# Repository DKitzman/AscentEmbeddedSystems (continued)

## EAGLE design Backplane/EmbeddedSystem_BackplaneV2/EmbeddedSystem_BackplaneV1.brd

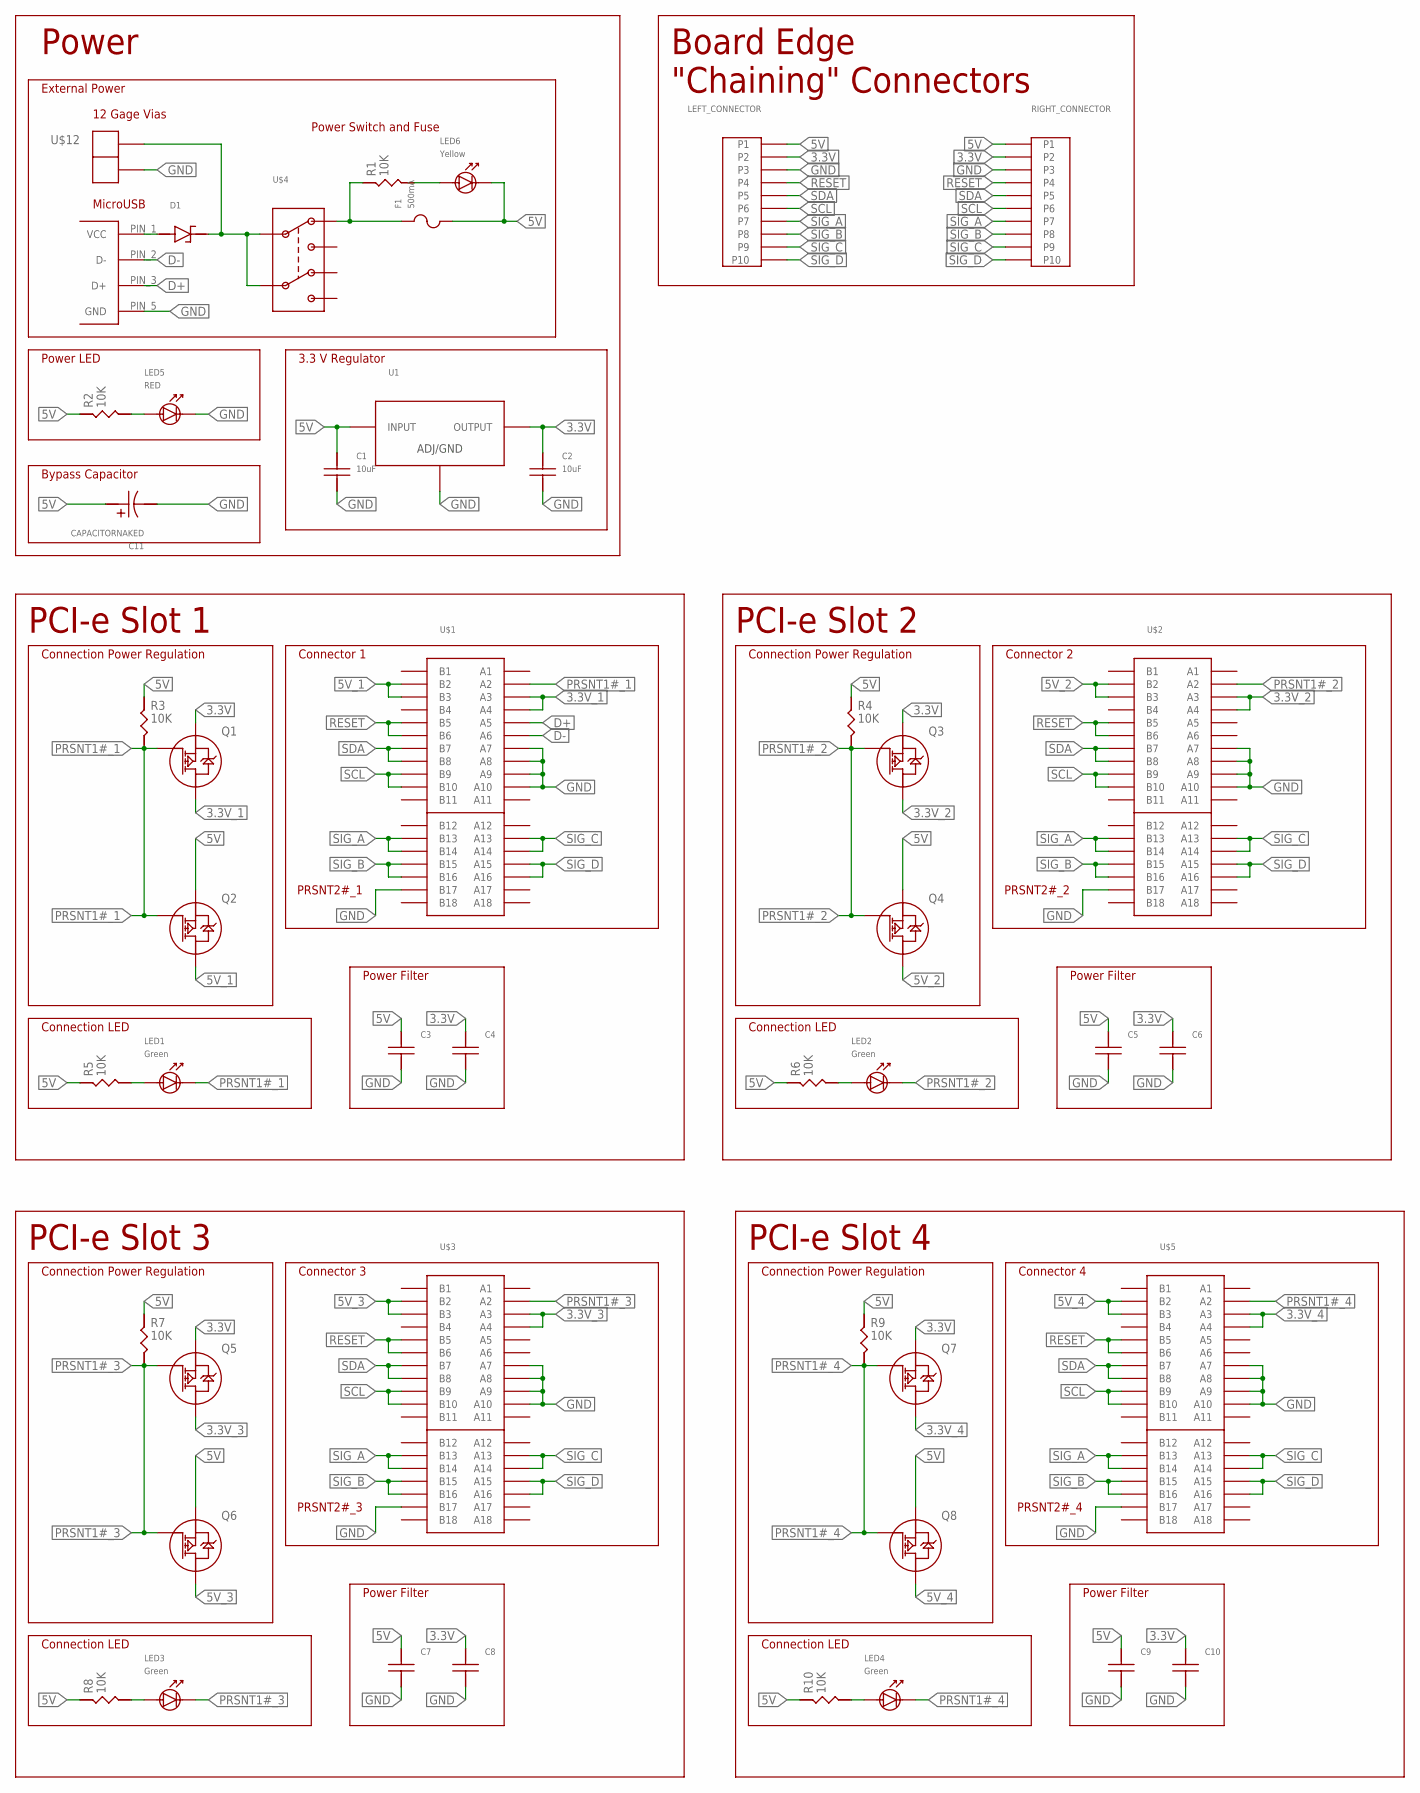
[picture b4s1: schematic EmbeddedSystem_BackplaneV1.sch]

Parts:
C1, C2: 10uF; 0805_STACKPOLERESISTOR
C3, C4, C5, C6, C7, C8, C9, C10: CAPACITOR-UNPOLARIZED0805; 0805_STACKPOLERESISTOR
C11: CAPACITORNAKED; ESK_H4_CAPACITOR_NAKED
D1: DIODE_SCHOTTKYSOD-123; SOD-123
F1: 500mA; TYPE_C1Q_FUSE
LED1, LED2, LED3, LED4: Green; 0805_LED
LED5: RED; 0805_LED
LED6: Yellow; 0805_LED
LEFT_CONNECTOR: 10PIN-HEADER; 10PIN_HEADER
Q1, Q2, Q3, Q4, Q5, Q6, Q7, Q8: PMOSSOT-23; SOT-23
R1, R2, R3, R4, R5, R6, R7, R8, R9, R10: 10K; 0805_STACKPOLERESISTOR
RIGHT_CONNECTOR: 10PIN-HEADER; 10PIN_HEADER
U1: VOLTAGE_REGULATOR; SOT223
U$1, U$2, U$3, U$5: PCI-E_X1; PCIE_X1
U$4: SWITCH_DPDT; SWITCH_GF-126
U$10: USBMICROB; USBMICROB-PAC
U$12: 2PIN-HEADER16GAGE; 2PIN_16GAGE

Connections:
3.3V: C2.P$1, C4.P$1, C6.P$1, C8.P$1, C10.P$1, LEFT_CONNECTOR.P2, Q1.S, Q3.S, Q5.S, Q7.S, RIGHT_CONNECTOR.P2, U1.P2 (OUTPUT), U1.TOP (OUTPUT)
3.3V_1: Q1.D, U$1.A3, U$1.A4
3.3V_2: Q3.D, U$2.A3, U$2.A4
3.3V_3: Q5.D, U$3.A3, U$3.A4
3.3V_4: Q7.D, U$5.A3, U$5.A4
5V: C1.P$1, C3.P$1, C5.P$1, C7.P$1, C9.P$1, C11.POSITIVE_PAD (POSITIVE_LEAD), F1.P$2, LED6.CATHODE, LEFT_CONNECTOR.P1, Q2.S, Q4.S, Q6.S, Q8.S, R2.P$1, R3.P$1, R4.P$1, R5.P$1, R6.P$1, R7.P$1, R8.P$1, R9.P$1, R10.P$1, RIGHT_CONNECTOR.P1, U1.P3 (INPUT)
5V_1: Q2.D, U$1.B2, U$1.B3
5V_2: Q4.D, U$2.B2, U$2.B3
5V_3: Q6.D, U$3.B2, U$3.B3
5V_4: Q8.D, U$5.B2, U$5.B3
5V_SUPPLY: D1.CATHODE, U$4.P1_C, U$4.P2_C, U$12.P1
D+: U$1.A5, U$10.PIN_3 (D+)
D-: U$1.A6, U$10.PIN_2 (D-)
GND: C1.P$2, C2.P$2, C3.P$2, C4.P$2, C5.P$2, C6.P$2, C7.P$2, C8.P$2, C9.P$2, C10.P$2, C11.NEGATIVE_PAD (NEGATIVE_LEAD), LED5.CATHODE, LEFT_CONNECTOR.P3, RIGHT_CONNECTOR.P3, U1.P1 (ADJ/GND), U$1.A7, U$1.A8, U$1.A9, U$1.A10, U$1.B17, U$2.A7, U$2.A8, U$2.A9, U$2.A10, U$2.B17, U$3.A7, U$3.A8, U$3.A9, U$3.A10, U$3.B17, U$5.A7, U$5.A8, U$5.A9, U$5.A10, U$5.B17, U$10.PIN_5 (GND), U$12.P2
unnamed: LED5.ANODE, R2.P$2
unnamed: F1.P$1, R1.P$1, U$4.P1_1
unnamed: LED6.ANODE, R1.P$2
unnamed: LED1.ANODE, R5.P$2
unnamed: D1.ANODE, U$10.PIN_1 (VCC)
unnamed: LED2.ANODE, R6.P$2
unnamed: LED3.ANODE, R8.P$2
unnamed: LED4.ANODE, R10.P$2
PRSNT1#_1: LED1.CATHODE, Q1.G (G(1)), Q2.G (G(1)), R3.P$2, U$1.A2
PRSNT1#_2: LED2.CATHODE, Q3.G (G(1)), Q4.G (G(1)), R4.P$2, U$2.A2
PRSNT1#_3: LED3.CATHODE, Q5.G (G(1)), Q6.G (G(1)), R7.P$2, U$3.A2
PRSNT1#_4: LED4.CATHODE, Q7.G (G(1)), Q8.G (G(1)), R9.P$2, U$5.A2
RESET: LEFT_CONNECTOR.P4, RIGHT_CONNECTOR.P4, U$1.B5, U$1.B6, U$2.B5, U$2.B6, U$3.B5, U$3.B6, U$5.B5, U$5.B6
SCL: LEFT_CONNECTOR.P6, RIGHT_CONNECTOR.P6, U$1.B9, U$1.B10, U$2.B9, U$2.B10, U$3.B9, U$3.B10, U$5.B9, U$5.B10
SDA: LEFT_CONNECTOR.P5, RIGHT_CONNECTOR.P5, U$1.B7, U$1.B8, U$2.B7, U$2.B8, U$3.B7, U$3.B8, U$5.B7, U$5.B8
SIG_A: LEFT_CONNECTOR.P7, RIGHT_CONNECTOR.P7, U$1.B13, U$1.B14, U$2.B13, U$2.B14, U$3.B13, U$3.B14, U$5.B13, U$5.B14
SIG_B: LEFT_CONNECTOR.P8, RIGHT_CONNECTOR.P8, U$1.B15, U$1.B16, U$2.B15, U$2.B16, U$3.B15, U$3.B16, U$5.B15, U$5.B16
SIG_C: LEFT_CONNECTOR.P9, RIGHT_CONNECTOR.P9, U$1.A13, U$1.A14, U$2.A13, U$2.A14, U$3.A13, U$3.A14, U$5.A13, U$5.A14
SIG_D: LEFT_CONNECTOR.P10, RIGHT_CONNECTOR.P10, U$1.A15, U$1.A16, U$2.A15, U$2.A16, U$3.A15, U$3.A16, U$5.A15, U$5.A16

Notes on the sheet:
Connector 1
PRSNT2#_1
Power LED
External Power
12 Gage Vias
MicroUSB
Power Switch and Fuse
3.3 V Regulator
Power
Connection LED
Connection Power Regulation
PCI-e Slot 1
Board Edge "Chaining" Connectors
Power Filter
Connector 2
PRSNT2#_2
PCI-e Slot 2
Connector 3
PRSNT2#_3
PCI-e Slot 3
Connector 4
PRSNT2#_4
PCI-e Slot 4
Bypass Capacitor

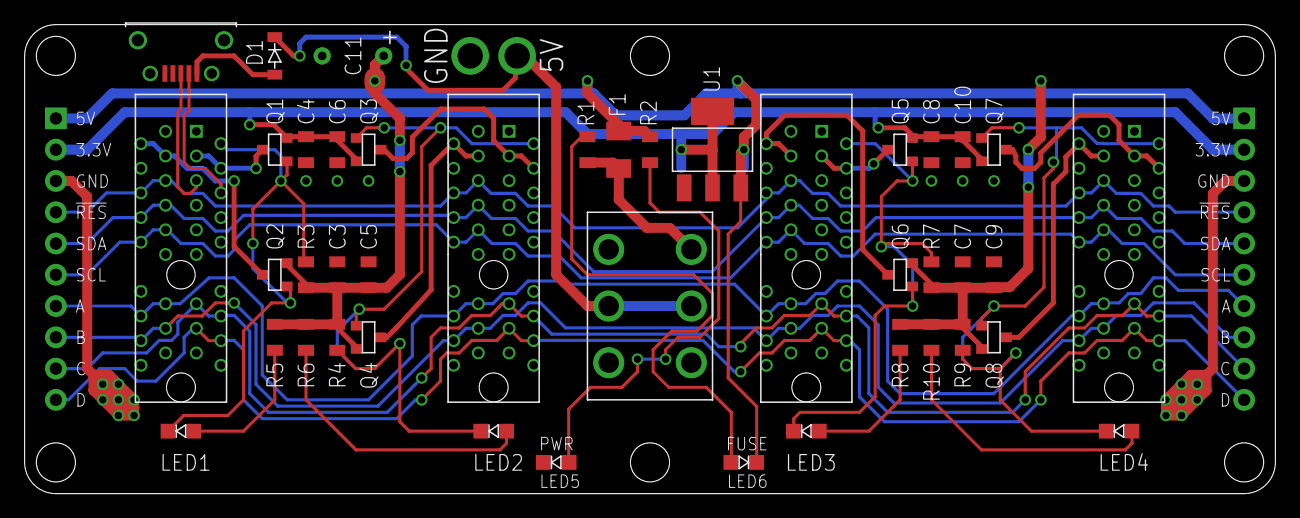
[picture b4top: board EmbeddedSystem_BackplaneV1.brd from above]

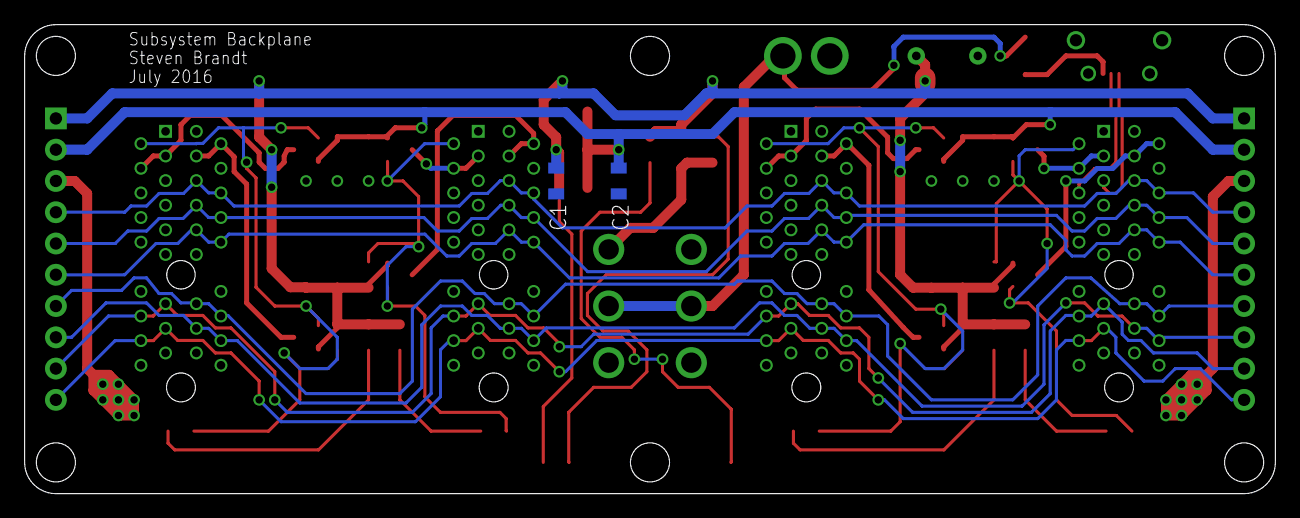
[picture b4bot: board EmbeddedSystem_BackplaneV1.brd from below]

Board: 2 copper layers, 101.6 x 38.1 mm, 47 parts (2 on the bottom side), 33 nets.

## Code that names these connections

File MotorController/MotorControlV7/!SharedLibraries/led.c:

#include <avr/io.h>
#include "led.h"

#define CMD_MASK (1<<2)
#define PING_MASK (1<<1)
#define ALIVE_MASK (1<<0)

/* /// PIN USAGE ///
PORTA - data out
PB0 - ALIVE
PB1 - PING
PB2 - CMD
 */

void led_init()
{
	PORTA.OUTSET = 0xFF;
	PORTA.DIRSET = 0xFF;

	PORTB.OUTSET = 0x07;
	PORTB.DIRSET = 0x07;
}

void led_cmdOn()
{
	PORTB.OUTCLR = CMD_MASK;
}
void led_cmdOff()
{
	PORTB.OUTSET = CMD_MASK;
}
void led_cmdToggle()
{
	PORTB.OUTTGL = CMD_MASK;
}

void led_pingOn()
{
	PORTB.OUTCLR = PING_MASK;
}
void led_pingOff()
{
	PORTB.OUTSET = PING_MASK;
}
void led_pingToggle()
{
	PORTB.OUTTGL = PING_MASK;
}

void led_aliveOn()
{
	PORTB.OUTCLR = ALIVE_MASK;
}
void led_aliveOff()
{
	PORTB.OUTSET = ALIVE_MASK;
}
void led_aliveToggle()
{
	PORTB.OUTTGL = ALIVE_MASK;
}

void led_dataOut(uint8_t value)
{
	PORTA.OUT = ~value;
}
void led_bitSet(uint8_t bit)
{
	PORTA.OUTCLR = (1<<bit);
}
void led_bitClear(uint8_t bit)
{
	PORTA.OUTSET = (1<<bit);
}
void led_bitToggle(uint8_t bit)
{
	PORTA.OUTTGL = (1<<bit);
}

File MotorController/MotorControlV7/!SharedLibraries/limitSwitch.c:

#include <avr/io.h>
#include "limitSwitch.h"

/* /// PERIPHERAL USAGE ///
 * None
 */

/* /// PIN USAGE ///
 * PE4	SW_A0
 * PE5	SW_B0
 *
 * PE6	SW_A1
 * PE7	SW_B1
 */

void limitSwitch_init()
{
	PORTE.DIRCLR = 0xF0;
	//Setting Pins 4-7 as totemPoll pullup
	PORTCFG.MPCMASK |= 0xF0;
	PORTE.PIN0CTRL = PORT_OPC_PULLUP_gc;
}

uint8_t atLimitA0()
{
	return (~PORTE.IN) & PIN4_bm;
}
uint8_t atLimitB0()
{
	return (~PORTE.IN) & PIN5_bm;
}

uint8_t atLimitA1()
{
	return (~PORTE.IN) & PIN6_bm;
}
uint8_t atLimitB1()
{
	return (~PORTE.IN) & PIN7_bm;
}

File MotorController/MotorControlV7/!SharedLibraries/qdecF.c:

#include <avr/io.h>
#include "qdecF.h"

#define DEGREES_PER_REV 360
#define CLOCK_CPU (uint32_t)32000000
#define PRESCALER 256

/* /// PERIPHERAL USAGE ///
 * TE0	qdec0 counter
 * TC1	freq0
 *
 * TF0	qdec1 counter
 * TD1	freq1
 */

/* /// PIN USAGE ///
 * PC4	QA0
 * PC5	QB0
 *
 * PD4	QA1
 * PD5	QB1
 */

static uint16_t cpr0 = 100;
static float lastVel0 = 0;

static uint16_t cpr1 = 100;
static float lastVel1 = 0;

void qdec_init(uint16_t cpr0p, uint16_t cpr1p)
{
	//Initializing qdec0
	cpr0 = cpr0p;
	PORTC.DIRCLR = PIN4_bm | PIN5_bm;

	// Set QDPH0 and QDPH1 sensing level.
	PORTCFG.MPCMASK = PIN4_bm | PIN5_bm;
	PORTC.PIN0CTRL = (PORTC.PIN0CTRL & ~PORT_ISC_gm) | PORT_ISC_LEVEL_gc;

	// Configure event
	EVSYS.CH0MUX = EVSYS_CHMUX_PORTC_PIN4_gc;
	EVSYS.CH0CTRL = EVSYS_QDEN_bm | EVSYS_DIGFILT_2SAMPLES_gc;

	// Configure TC as a quadrature counter.
	TCE0.CTRLD = (uint8_t) TC_EVACT_QDEC_gc | TC_EVSEL_CH0_gc;
	TCE0.CTRLA = TC_CLKSEL_DIV1_gc;

	// Configure channel 2 to input pin for freq calculation.
	EVSYS.CH1MUX = EVSYS_CHMUX_PORTC_PIN4_gc;
	EVSYS.CH1CTRL = EVSYS_DIGFILT_4SAMPLES_gc;

	// Configure TC to capture frequency.
	TCC1.CTRLD = (uint8_t) TC_EVACT_FRQ_gc | TC_EVSEL_CH1_gc;
	TCC1.CTRLB = TC1_CCAEN_bm;
	TCC1.CTRLA = TC_CLKSEL_DIV256_gc;


	//Initializing qdec1 
	cpr1 = cpr1p;
	PORTD.DIRCLR = PIN4_bm | PIN5_bm;

	// Set QDPH0 and QDPH1 sensing level.
	PORTCFG.MPCMASK = PIN4_bm | PIN5_bm;
	PORTD.PIN0CTRL = (PORTD.PIN0CTRL & ~PORT_ISC_gm) | PORT_ISC_LEVEL_gc;

	// Configure event
	EVSYS.CH2MUX = EVSYS_CHMUX_PORTD_PIN4_gc;
	EVSYS.CH2CTRL = EVSYS_QDEN_bm | EVSYS_DIGFILT_2SAMPLES_gc;

	// Configure TC as a quadrature counter.
	TCF0.CTRLD = (uint8_t) TC_EVACT_QDEC_gc | TC_EVSEL_CH2_gc;
	TCF0.CTRLA = TC_CLKSEL_DIV1_gc;

	// Configure channel 3 to input pin for freq calculation.
	EVSYS.CH3MUX = EVSYS_CHMUX_PORTD_PIN4_gc;
	EVSYS.CH3CTRL = EVSYS_DIGFILT_4SAMPLES_gc;

	// Configure TC to capture frequency.
	TCD1.CTRLD = (uint8_t) TC_EVACT_FRQ_gc | TC_EVSEL_CH3_gc;
	TCD1.CTRLB = TC1_CCAEN_bm;
	TCD1.CTRLA = TC_CLKSEL_DIV256_gc;

}

uint16_t qdec_pos0()
{
	return TCE0.CNT;
}
uint16_t qdec_pos1()
{
	return TCF0.CNT;
}

float qdec_vel0()
{
	if(TCC1.INTFLAGS & TC1_OVFIF_bm)
	{
		//TCC1.INTFLAGS |= TC1_OVFIF_bm;
		lastVel0 = 0;
	}
	else if(TCC1.INTFLAGS & TC1_CCAIF_bm)
	{
		lastVel0 = (DEGREES_PER_REV*(CLOCK_CPU/PRESCALER))/((float)cpr0*TCC1.CCA);
		if (TCE0.CTRLFSET & TC0_DIR_bm) //Yes, this should be TCE0 ('quadrature timer)
		{
			//We're going clockwise (negative)
			lastVel0*=-1;
		}
	}//else - No new velocity, use the last one

	return lastVel0;
}
float qdec_vel1()
{
	if(TCD1.INTFLAGS & TC1_OVFIF_bm)
	{
		lastVel1 = 0;
	}
	else if(TCD1.INTFLAGS & TC1_CCAIF_bm)
	{
		lastVel1 = (DEGREES_PER_REV*(CLOCK_CPU/PRESCALER))/((float)cpr1*TCD1.CCA);
		if (TCF0.CTRLFSET & TC0_DIR_bm) //Yes, this should be TCF0 (quadrature timer)
		{
			//We're going clockwise (negative)
			lastVel1*=-1;
		}
	}//else - No new velocity, use the last one

	return lastVel1;
}

uint8_t qdec_dir0()
{
	if (TCE0.CTRLFSET & TC0_DIR_bm)
	{
		return CW_DIR;
	}
	else
	{
		return CCW_DIR;
	}
}
uint8_t qdec_dir1()
{
	if (TCF0.CTRLFSET & TC0_DIR_bm)
	{
		return CW_DIR;
	}
	else
	{
		return CCW_DIR;
	}
}

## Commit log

2017-06-15 Initial commit for ES code. Missing motor controller code.
2017-06-21 Adding motor controller code and eagle files for backplane, launchpad carrier, and GPS
2017-07-11 added pcb files for soil sensor.
